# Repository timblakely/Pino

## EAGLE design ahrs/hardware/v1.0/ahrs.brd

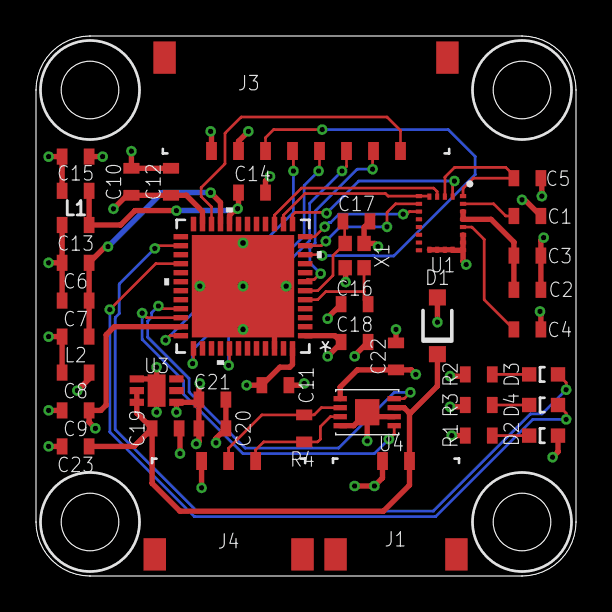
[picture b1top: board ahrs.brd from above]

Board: 4 copper layers, 30.0 x 30.0 mm, 41 parts (0 on the bottom side), 30 nets.

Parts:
C1, C3, C5, C6, C8, C9, C10, C13, C15: 0.1uF 10V; C0603
C2: 10uF 10V; C0603
C4: 10nF 16v; C0603
C7, C14, C18, C19: 1uF 10v; C0603
C11: 100nF 10v; C0603
C12: 4.7uF 10v; C0603
C16, C17: 10pF 10v; C0603
C20, C21: 2.2uF 10V; C0603
C22, C23: 0.1uF 10v; C0603
D1: SOD123
D2, D3, D4: 150060BS75000; D0603
J1: LINEAR_2_5040500291; MOLEX_5040500291
J3: LINEAR_85040500891; MOLEX_5040500891
J4: LINEAR_35040500391; MOLEX_5040500391
L1, L2: 600R@100MHz; L0603
R1, R2, R3: 22; R0603
R4: R0603
U1: LSM9DS1; LGA24_3.5X3X1
U2: STM32G4_UFQFPN48_T1; UFQFPN-48_7X7X0P55MM
U3: LDFM33PUR; DFN6_2X2
U4: MCP2542FD; TDFN_2X3
X1: CRYSTAL_NX2016SA-24MHZ-EXS00A-CS11335; NX201SA

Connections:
+3V3: C2.1, C3.1, C5.1, C8.1, C9.1, C10.1, C11.1, C12.1, C15.1, C18.1, C20.1, C21.1, C22.1, D2.2, J3.P1, L1.1, L2.2, U1.P$22, U1.P$23, U2.1, U2.23, U2.35, U2.48, U3.PIN1, U4.5
+5V: C19.1, C23.1, D1.C, J1.P1, U3.PIN5, U3.PIN6, U4.3
CAN_RX: U2.33, U4.4
CAN_TX: U2.34, U4.1
CS_AG: U1.P$7, U2.11
CS_M: U1.P$8, U2.12
GND: C1.1, C2.2, C3.2, C4.1, C6.2, C7.2, C8.2, C9.2, C10.2, C11.2, C12.2, C13.2, C14.2, C15.2, C16.2, C17.2, C18.2, C19.2, C20.2, C21.2, C22.2, C23.2, D1.A, J1.P2, J3.P2, J4.P3, R1.1, R2.2, R3.2, U1.P$14, U1.P$15, U1.P$16, U1.P$17, U1.P$18, U1.P$19, U1.P$20, U2.46, U2.49, U3.PAD, U3.PIN4, U4.2, U4.8, U4.PAD, X1.P$2, X1.P$4
LPUART_RX: J3.P8, U2.22
LPUART_TX: J3.P3, U2.10
MISO: U1.P$5, U1.P$6, U2.14
MOSI: U1.P$4, U2.15
unnamed: D2.1, R1.2
unnamed: C1.2, U1.P$24
unnamed: C4.2, U1.P$21
unnamed: C5.2, U1.P$1, U1.P$3
unnamed: C17.1, U2.6, X1.P$1
unnamed: C16.1, U2.5, X1.P$3
unnamed: D4.2, U2.28
unnamed: D3.2, U2.26
unnamed: D3.1, R2.1
unnamed: D4.1, R3.1
unnamed: J4.P1, R4.2, U4.7
unnamed: J4.P2, R4.1, U4.6
NRST: J3.P7, U2.7
SCK: U1.P$2, U2.13
SWCLK: J3.P5, U2.37
SWDIO: J3.P4, U2.36
SWO: J3.P6, U2.41
VDDA: C6.1, C7.1, L2.1, U2.21
VREF: C13.1, C14.1, L1.2, U2.20

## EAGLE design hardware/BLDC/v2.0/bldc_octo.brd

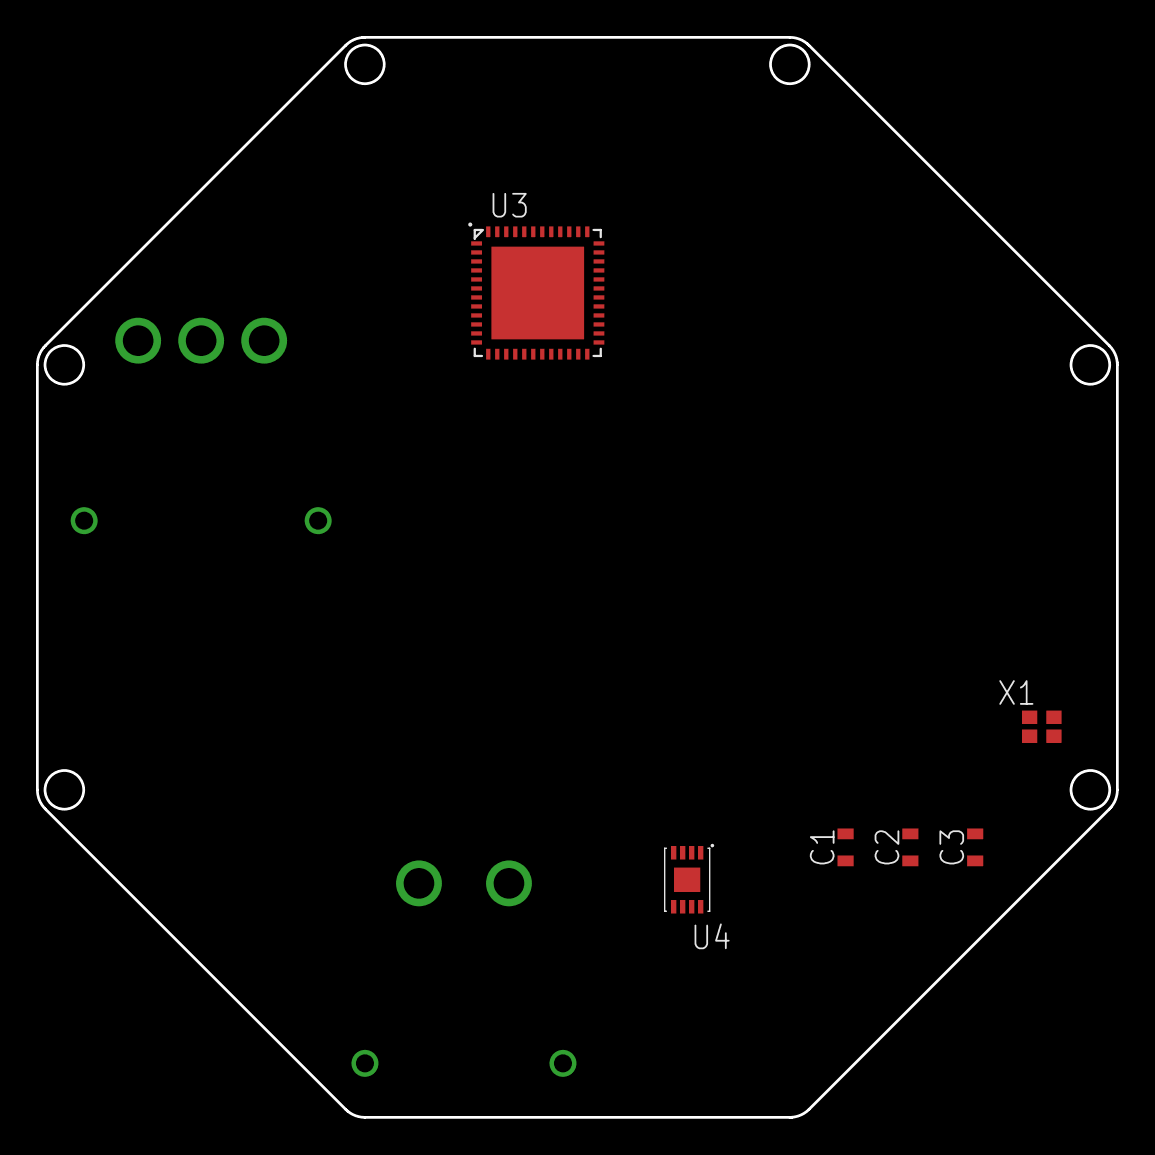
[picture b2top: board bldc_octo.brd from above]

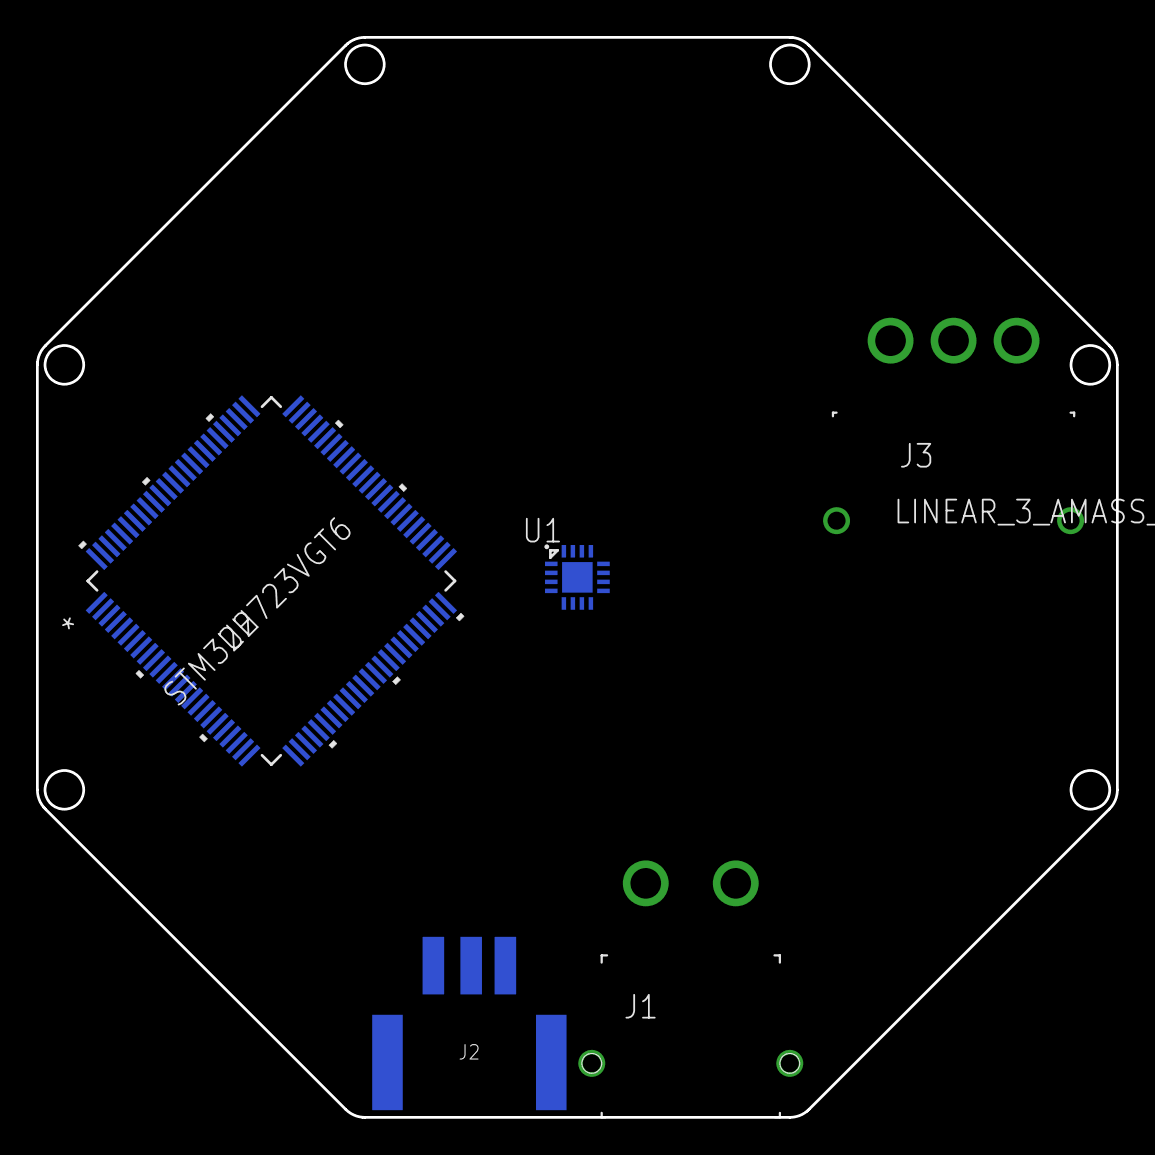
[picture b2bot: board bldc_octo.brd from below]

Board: 4 copper layers, 60.0 x 60.0 mm, 11 parts (5 on the bottom side), 6 nets, no tracks yet.

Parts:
C1: C0603
C2, C3: 10pf 10V; C0603
J1: PWR_2_XT30PW-M; XT30PW-M
J2: LINEAR_3_MOLEX_5023520300; MOLEX_5023520300
J3: LINEAR_3_AMASS_MR30PW-M; MR30PW-M
U1: MA702; QFN-16_3X3
U2: STM32H723VGT6; LQFP100_STM
U3: DRV8323RS; VQFN-48_7X7
U4: MCP2542FD; TDFN_2X3
X1: CRYSTAL_NX2016SA-24MHZ-EXS00A-CS11335; NX201SA

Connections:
GND: C1.2, C2.2, C3.2, J1.P$1, J2.P$3, X1.P$2, X1.P$4
unnamed: J2.P$1, U4.7
unnamed: J2.P$2, U4.6
unnamed: C2.1, U2.13, X1.P$1
unnamed: C3.1, U2.12, X1.P$3
NRST: C1.1, U2.14

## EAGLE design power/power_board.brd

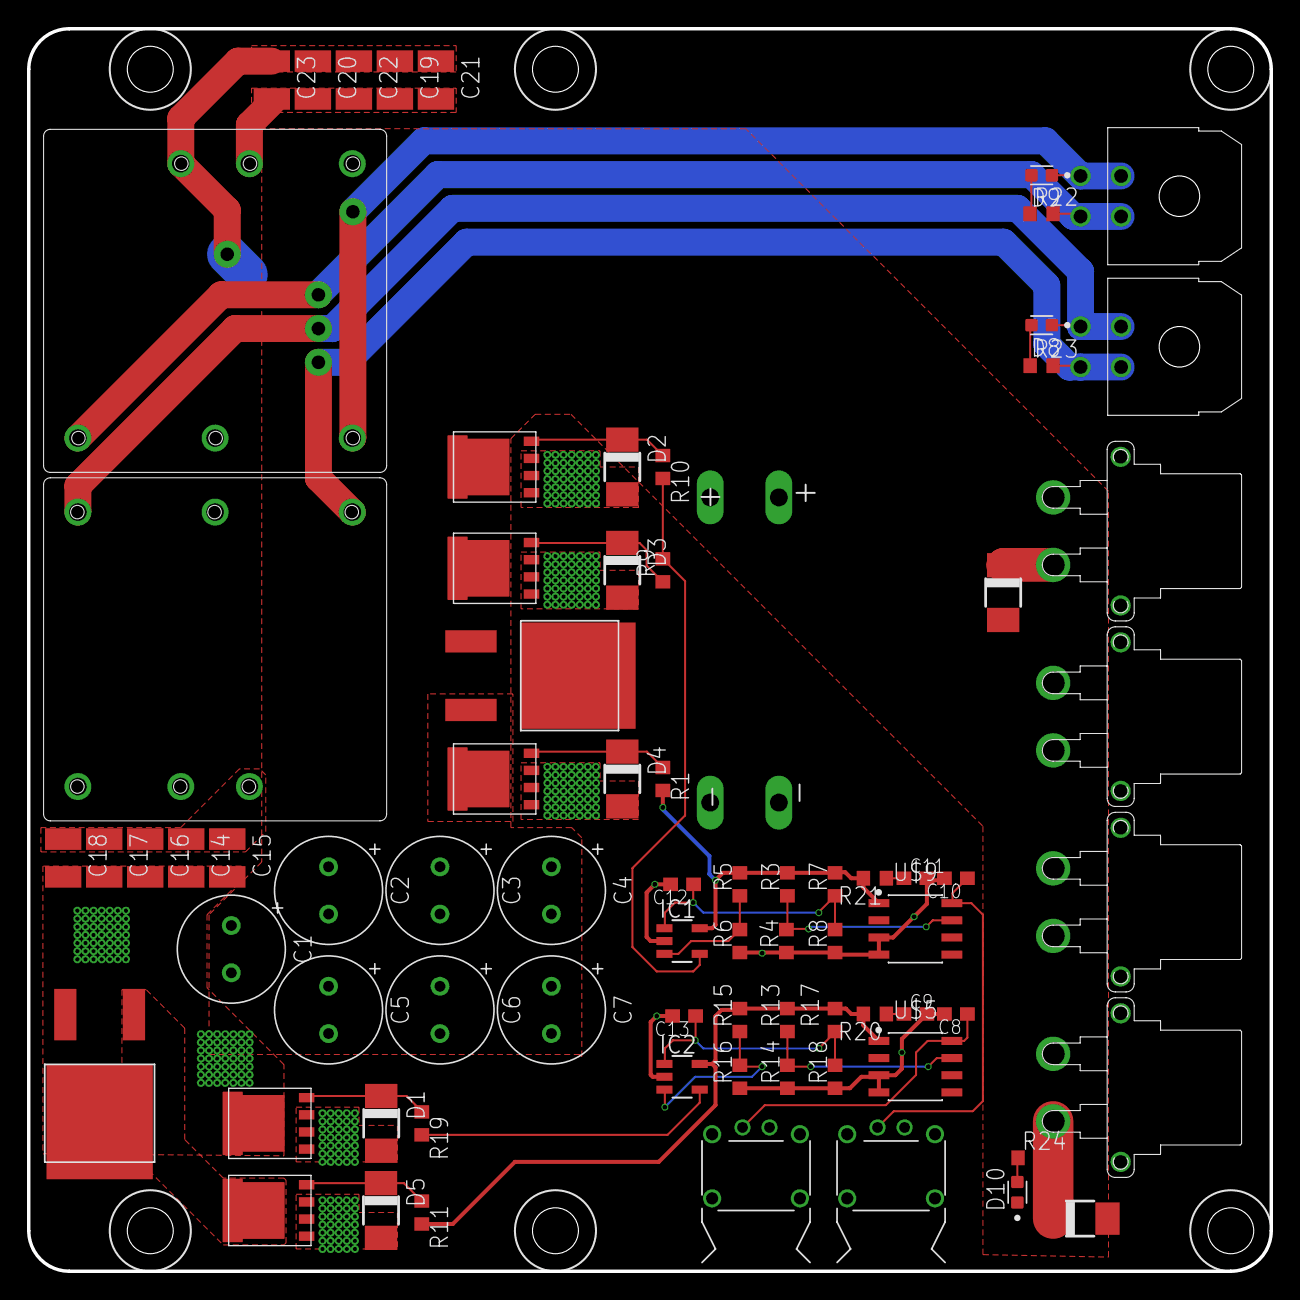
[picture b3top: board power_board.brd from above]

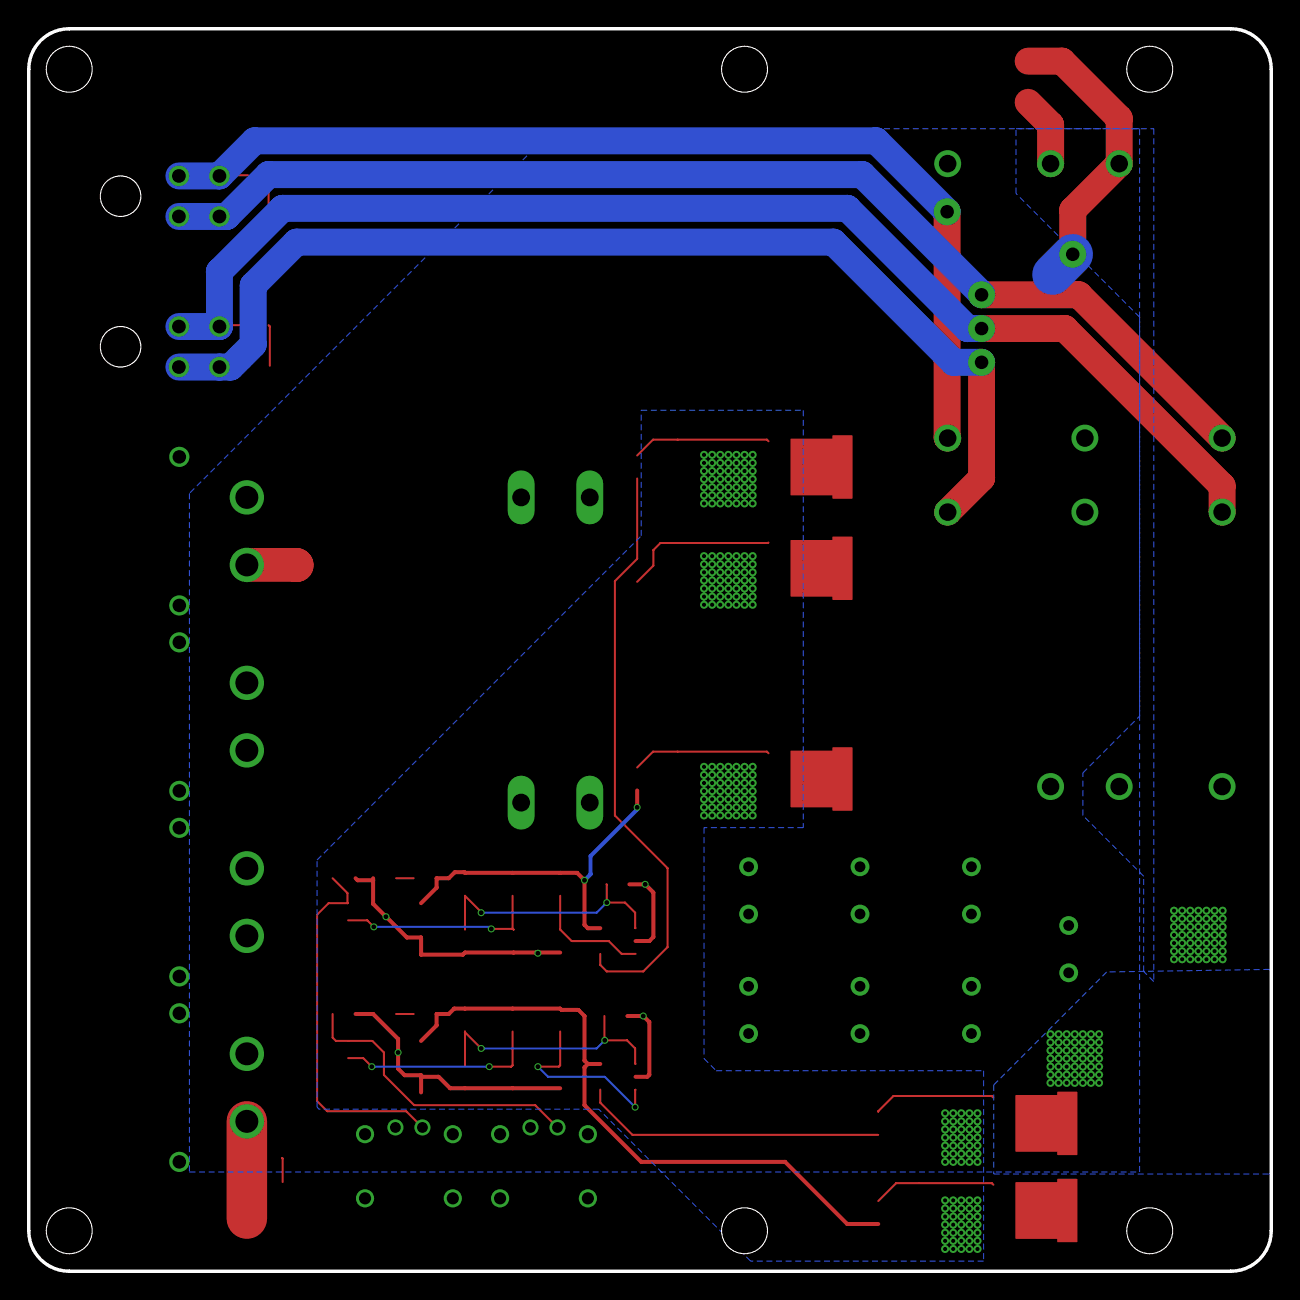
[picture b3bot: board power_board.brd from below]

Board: 2 copper layers, 92.0 x 92.0 mm, 78 parts (2 on the bottom side), 32 nets.

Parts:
C1, C2, C3, C4, C5, C6, C7: 220uf; C_ELEC_8X11_5
C8, C9, C10, C11: 2.2uF; C0603
C12, C13: 300nF; C0603
C14, C15, C16, C17, C18, C19, C20, C21, C22, C23: 10uF; C1210
D1, D2, D3, D4, D5: SMAJ12A; DO-214AC
D6, D7: SK510A-LTP; DO-214AC
D8, D9: LTST-C191TBKT
D10: LTST-C191KRKT; LTST-C191TBKT
IC1, IC2: LM321MF; SOT23-5
J1, J2: FASTON1289_ST; FASTON_1289-ST
J3: 12v; MOLEX_4_RA
J4: 5v; MOLEX_4_RA
J5, J6, J7, J8: XT30PW-F
R1, R9, R10, R11, R19: 4.7k; R0603
R2, R12: 2; PWR163
R3, R13: 873.1k; R0603
R4, R14: 100k; R0603
R5, R7, R15, R17: 100k\; R0603
R6, R16: 400k; R0603
R8, R18: 500k; R0603
R20, R21: 0.5; R0603
R22, R23, R24: 470; R0603
U1: PDQ30-Q24-S5-D; PDQ30-D
U2: PDQ30-Q24-S12-D; PDQ30-D
U$1, U$2, U$3, U$6, U$11: PSMN1R0-40YSH; LFPAK56E
U$5, U$9: LP2951ACMM/NOPB; LP2591
U$26, U$27: 2-PIN; M80-8420242

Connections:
5V_GND: D8.C, J4.CIRCUIT1, J4.CIRCUIT3, U1.P$5
12V_GND: D9.C, J3.CIRCUIT1, J3.CIRCUIT3, U2.P$5
+5VOUT: J4.CIRCUIT2, J4.CIRCUIT4, R23.2, U1.P$3
+12VOUT: J3.CIRCUIT2, J3.CIRCUIT4, R22.2, U2.P$3
BATT_+24V: C1.1, C2.1, C3.1, C4.1, C5.1, C6.1, C7.1, C14.1, C15.1, C16.1, C17.1, C18.1, C19.1, C20.1, C21.1, C22.1, C23.1, D6.C, D7.C, J1.P$1, J1.P$2, J5.P$2, J6.P$2, J7.P$2, J8.P$2, R24.2, U1.P$1, U2.P$1, U$26.1, U$27.1
BATT_GND: C8.2, C9.2, C10.2, C11.2, C12.2, C13.2, D1.A, D2.A, D3.A, D4.A, D5.A, IC1.2, IC2.2, J2.P$1, J2.P$2, R4.1, R6.1, R8.1, R14.1, R16.1, R18.1, U$1.1, U$1.2, U$1.3, U$2.1, U$2.2, U$2.3, U$3.1, U$3.2, U$3.3, U$5.3, U$5.4, U$6.1, U$6.2, U$6.3, U$9.3, U$9.4, U$11.1, U$11.2, U$11.3
ISO_12V: IC2.5, R11.2, R13.2, R15.2, R17.2, R20.2, U$5.1
ISO_GND: C14.2, C15.2, C16.2, C17.2, C18.2, C19.2, C20.2, C21.2, C22.2, C23.2, R12.P$2, U1.P$2, U2.P$2, U$6.5
LEG_12V: IC1.5, R1.2, R3.2, R5.2, R7.2, R21.2, U$9.1
LEG_GND: C1.2, C2.2, C3.2, C4.2, C5.2, C6.2, C7.2, D6.A, D7.A, D10.C, J5.P$1, J6.P$1, J7.P$1, J8.P$1, R2.P$1, U$1.5, U$2.5
unnamed: R2.P$2, U$11.5
unnamed: D4.C, R1.1, U$11.4
unnamed: R3.1, R4.2, U$9.7
unnamed: IC1.3, R5.1, R6.2
unnamed: C12.1, IC1.1, R7.1, R8.2
unnamed: IC1.4, R9.2, R10.2
unnamed: D5.C, R11.1, U$3.4
unnamed: D3.C, R9.1, U$1.4
unnamed: D2.C, R10.1, U$2.4
unnamed: R13.1, R14.2, U$5.7
unnamed: R12.P$1, U$3.5
unnamed: IC2.3, R15.1, R16.2
unnamed: C13.1, IC2.1, R17.1, R18.2
unnamed: IC2.4, R19.2
unnamed: D1.C, R19.1, U$6.4
unnamed: C9.1, R20.1
unnamed: C11.1, R21.1
unnamed: C8.1, U$5.8, U$26.2
unnamed: C10.1, U$9.8, U$27.2
unnamed: D9.A, R22.1
unnamed: D8.A, R23.1
unnamed: D10.A, R24.1

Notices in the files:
parts and their libraries:
COPYRIGHT: Copyright (C) 2016 Accelerated Designs. All rights reserved
COPYRIGHT: Copyright (C) 2018 Accelerated Designs. All rights reserved
